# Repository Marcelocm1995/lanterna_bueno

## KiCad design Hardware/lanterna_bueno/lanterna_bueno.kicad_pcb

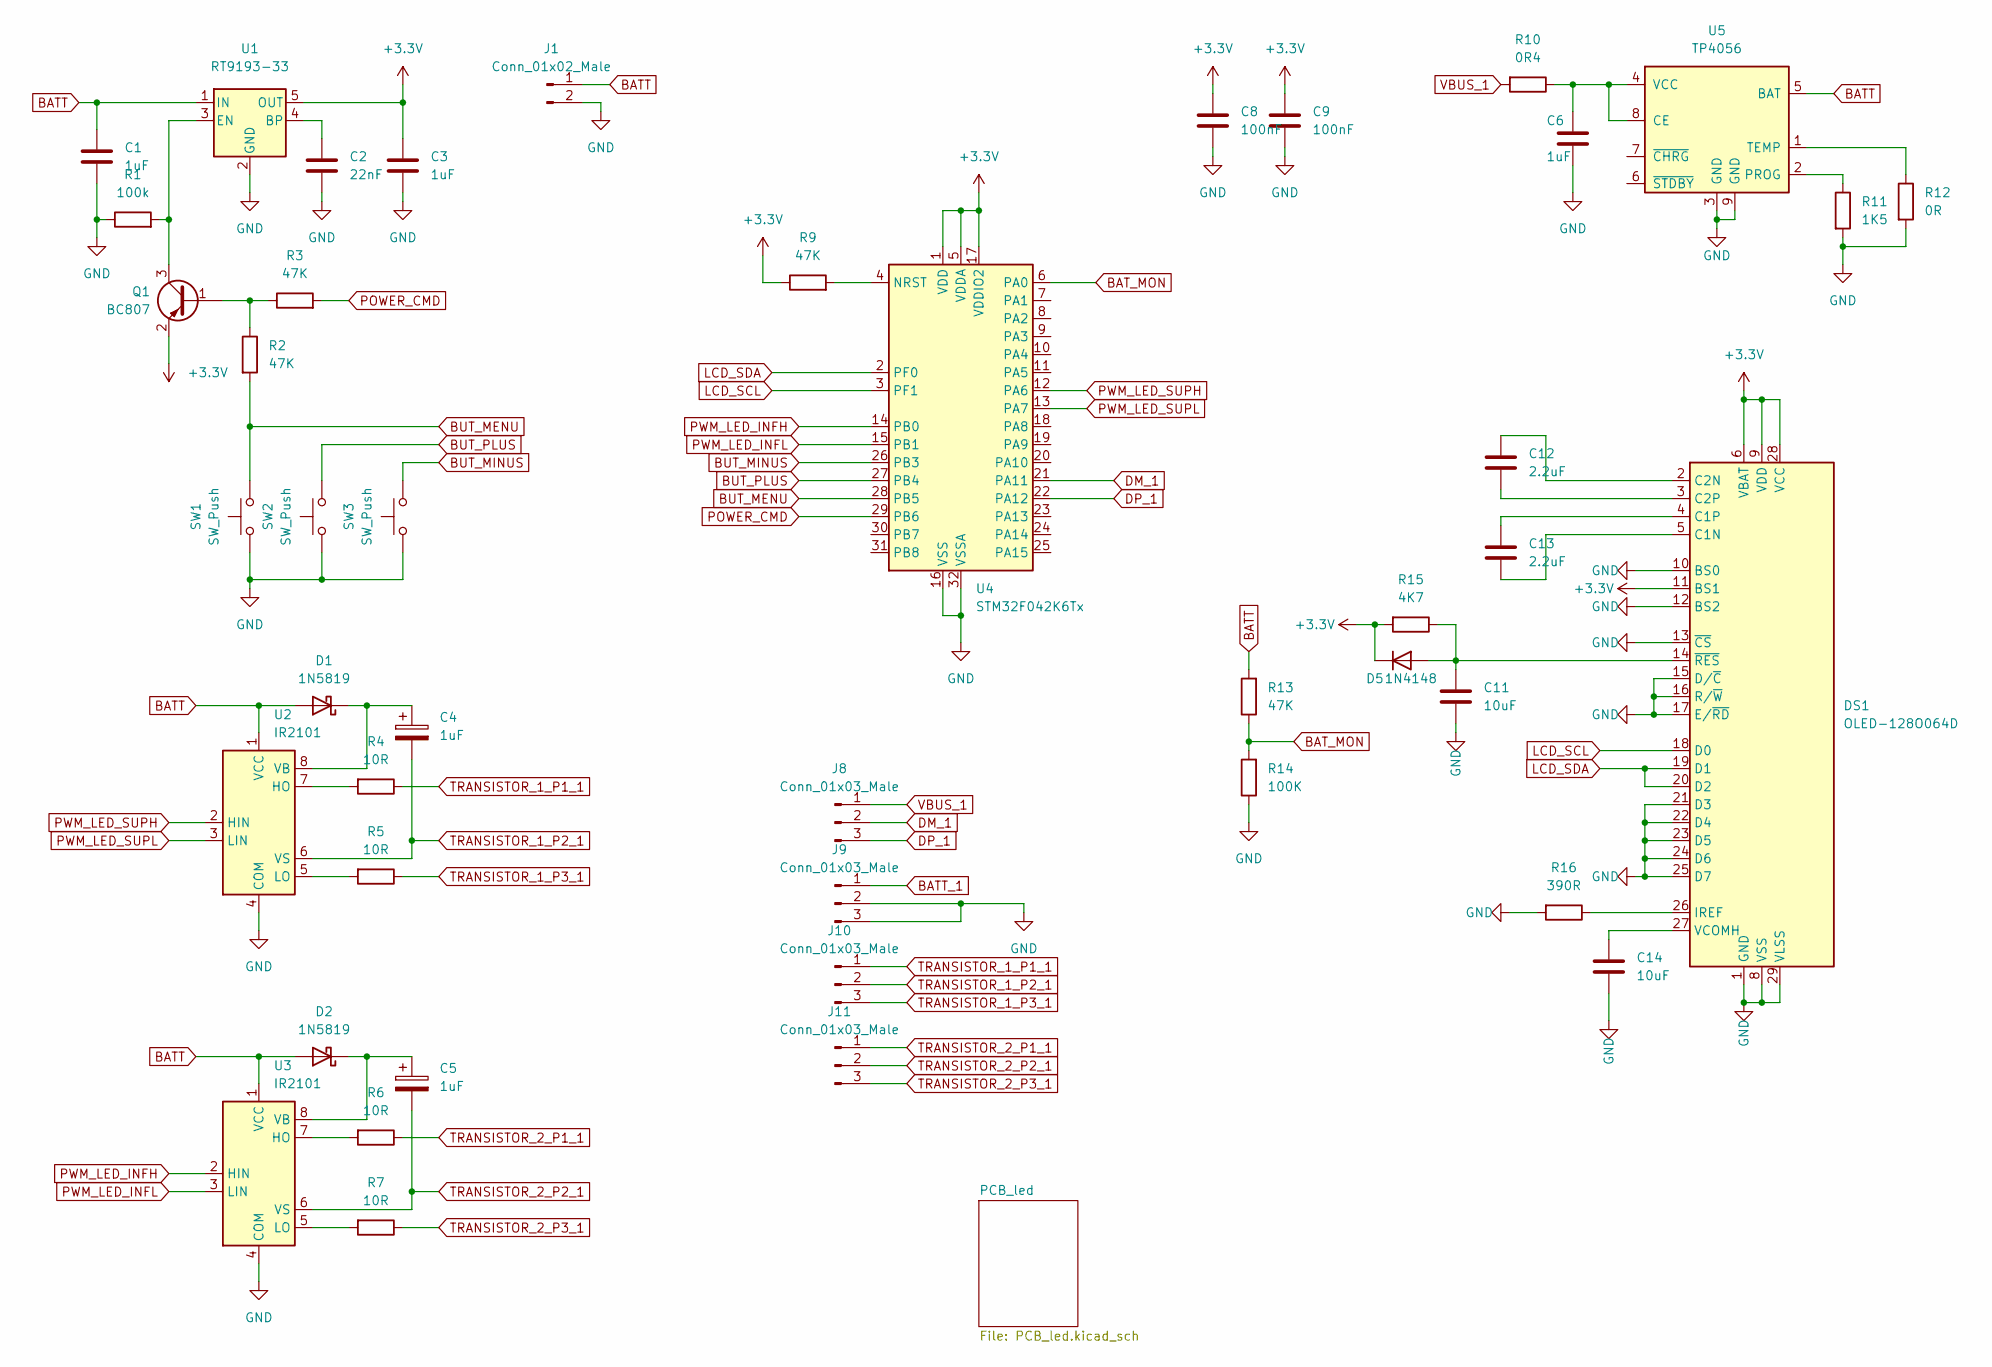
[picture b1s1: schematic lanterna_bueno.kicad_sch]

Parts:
C1, C3, C6: 1uF; C_1206_3216Metric
C2: 22nF; C_0603_1608Metric
C4, C5: 1uF; CP_Elec_4x3
C8, C9: 100nF; C_0603_1608Metric
C11, C14: 10uF; C_1206_3216Metric
C12, C13: 2.2uF; C_0603_1608Metric
D1, D2: 1N5819; D_SMA
D5: 1N4148; D_SOD-123
DS1: OLED-128O064D
J1: Conn_01x02_Male; SMD_BAT
J8, J9, J10, J11: Conn_01x03_Male; 3pin 90 pcb solder
Q1: BC807; SOT-23
R1: 100k; R_0603_1608Metric
R2, R3, R9, R13: 47K; R_0603_1608Metric
R4, R5, R6, R7: 10R; R_0603_1608Metric
R10: 0R4; R_0603_1608Metric
R11: 1K5; R_0603_1608Metric
R12: 0R; R_0603_1608Metric
R14: 100K; R_0603_1608Metric
R15: 4K7; R_0603_1608Metric
R16: 390R; R_0603_1608Metric
SW1, SW2, SW3: SW_Push; SW_Push_1P1T_NO_6x6mm_H9.5mm
U1: RT9193-33; SOT-23-5
U2, U3: IR2101; SOIC-8_3.9x4.9mm_P1.27mm
U4: STM32F042K6Tx; LQFP-32_7x7mm_P0.8mm
U5: TP4056; Infineon_PG-DSO-8-43

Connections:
+3V3: C3.1, C8.1, C9.1, D5.1 (K), DS1.6 (VBAT), DS1.9 (VDD), DS1.11 (BS1), DS1.28 (VCC), Q1.2 (E), R9.1, R15.2, U1.5 (OUT), U4.1 (VDD), U4.5 (VDDA), U4.17 (VDDIO2)
BATT: C1.1, D1.2 (A), D2.2 (A), J1.1, R13.2, U1.1 (IN), U2.1 (VCC), U3.1 (VCC), U5.5 (BAT)
BATT_1: J9.1
BAT_MON: R13.1, R14.2, U4.6 (PA0)
BUT_MENU: R2.2, SW1.2, U4.28 (PB5)
BUT_MINUS: SW3.2, U4.26 (PB3)
BUT_PLUS: SW2.2, U4.27 (PB4)
DM_1: J8.2, U4.21 (PA11)
DP_1: J8.3, U4.22 (PA12)
GND: C1.2, C2.2, C3.2, C6.2, C8.2, C9.2, C11.2, C14.2, DS1.1 (GND), DS1.8 (VSS), DS1.10 (BS0), DS1.12 (BS2), DS1.13 (~CS), DS1.15 (D/~C), DS1.16 (R/~W), DS1.17 (E/~RD), DS1.21 (D3), DS1.22 (D4), DS1.23 (D5), DS1.24 (D6), DS1.25 (D7), DS1.29 (VLSS), DS1.30 (GND), J1.2, J9.2, J9.3, R1.1, R11.2, R12.2, R14.1, R16.2, SW1.1, SW2.1, SW3.1, U1.2 (GND), U2.4 (COM), U3.4 (COM), U4.16 (VSS), U4.32 (VSSA), U5.3 (GND), U5.9 (GND)
LCD_SCL: DS1.18 (D0), U4.3 (PF1)
LCD_SDA: DS1.19 (D1), DS1.20 (D2), U4.2 (PF0)
unnamed: C2.1, U1.4 (BP)
unnamed: C4.1, D1.1 (K), U2.8 (VB)
unnamed: C5.1, D2.1 (K), U3.8 (VB)
unnamed: C6.1, R10.1, U5.4 (VCC), U5.8 (CE)
unnamed: C11.1, D5.2 (A), DS1.14 (~RES), R15.1
unnamed: C12.1, DS1.2 (C2N)
unnamed: C12.2, DS1.3 (C2P)
unnamed: C13.1, DS1.4 (C1P)
unnamed: C13.2, DS1.5 (C1N)
unnamed: C14.1, DS1.27 (VCOMH)
unnamed: DS1.26 (IREF), R16.1
unnamed: Q1.1 (B), R2.1, R3.1
unnamed: Q1.3 (C), R1.2, U1.3 (EN)
unnamed: R4.2, U2.7 (HO)
unnamed: R5.2, U2.5 (LO)
unnamed: R6.2, U3.7 (HO)
unnamed: R7.2, U3.5 (LO)
unnamed: R9.2, U4.4 (NRST)
unnamed: R11.1, U5.2 (PROG)
unnamed: R12.1, U5.1 (TEMP)
POWER_CMD: R3.2, U4.29 (PB6)
PWM_LED_INFH: U3.2 (HIN), U4.14 (PB0)
PWM_LED_INFL: U3.3 (LIN), U4.15 (PB1)
PWM_LED_SUPH: U2.2 (HIN), U4.12 (PA6)
PWM_LED_SUPL: U2.3 (LIN), U4.13 (PA7)
TRANSISTOR_1_P1_1: J10.1, R4.1
TRANSISTOR_1_P2_1: C4.2, J10.2, U2.6 (VS)
TRANSISTOR_1_P3_1: J10.3, R5.1
TRANSISTOR_2_P1_1: J11.1, R6.1
TRANSISTOR_2_P2_1: C5.2, J11.2, U3.6 (VS)
TRANSISTOR_2_P3_1: J11.3, R7.1
VBUS_1: J8.1, R10.2

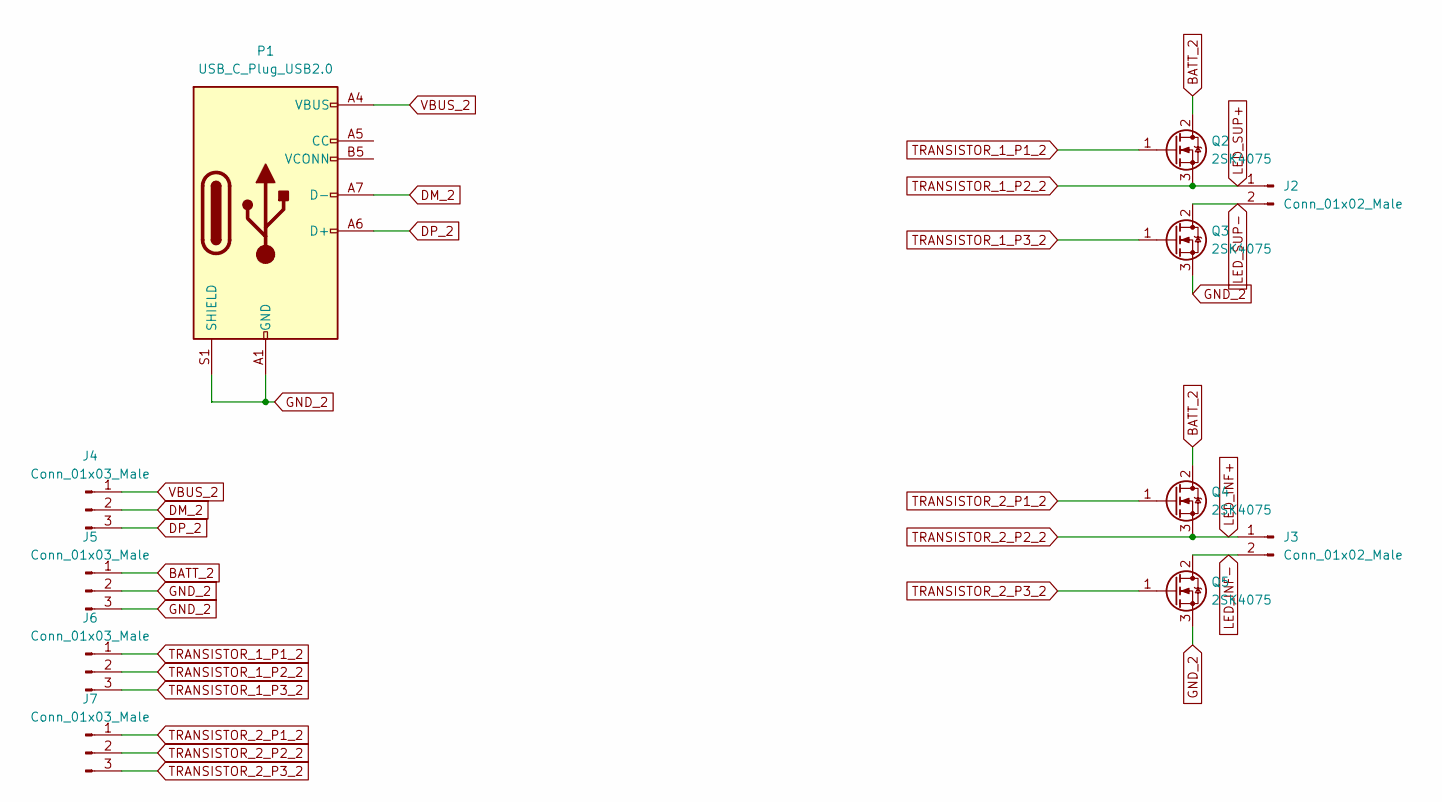
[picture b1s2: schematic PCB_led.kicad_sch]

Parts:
J2, J3: Conn_01x02_Male; SMD_BAT
J4, J5, J6, J7: Conn_01x03_Male; 3pin 90 pcb solder
P1: USB_C_Plug_USB2.0; USB_C_Receptacle_HRO_TYPE-C-31-M-12
Q2, Q3, Q4, Q5: 2SK4075; TO-252-2

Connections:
BATT_2: J5.1, Q2.2 (D), Q4.2 (D)
DM_2: J4.2, P1.A7 (D-)
DP_2: J4.3, P1.A6 (D+)
GND_2: J5.2, J5.3, P1.A1 (GND), P1.A12 (GND), P1.B1 (GND), P1.B12 (GND), P1.S1 (SHIELD), Q3.3 (S), Q5.3 (S)
LED_INF+: J3.1, J7.2, Q4.3 (S)
LED_INF-: J3.2, Q5.2 (D)
LED_SUP+: J2.1, J6.2, Q2.3 (S)
LED_SUP-: J2.2, Q3.2 (D)
TRANSISTOR_1_P1_2: J6.1, Q2.1 (G)
TRANSISTOR_1_P3_2: J6.3, Q3.1 (G)
TRANSISTOR_2_P1_2: J7.1, Q4.1 (G)
TRANSISTOR_2_P3_2: J7.3, Q5.1 (G)
VBUS_2: J4.1, P1.A4 (VBUS), P1.A9 (VBUS), P1.B4 (VBUS), P1.B9 (VBUS)

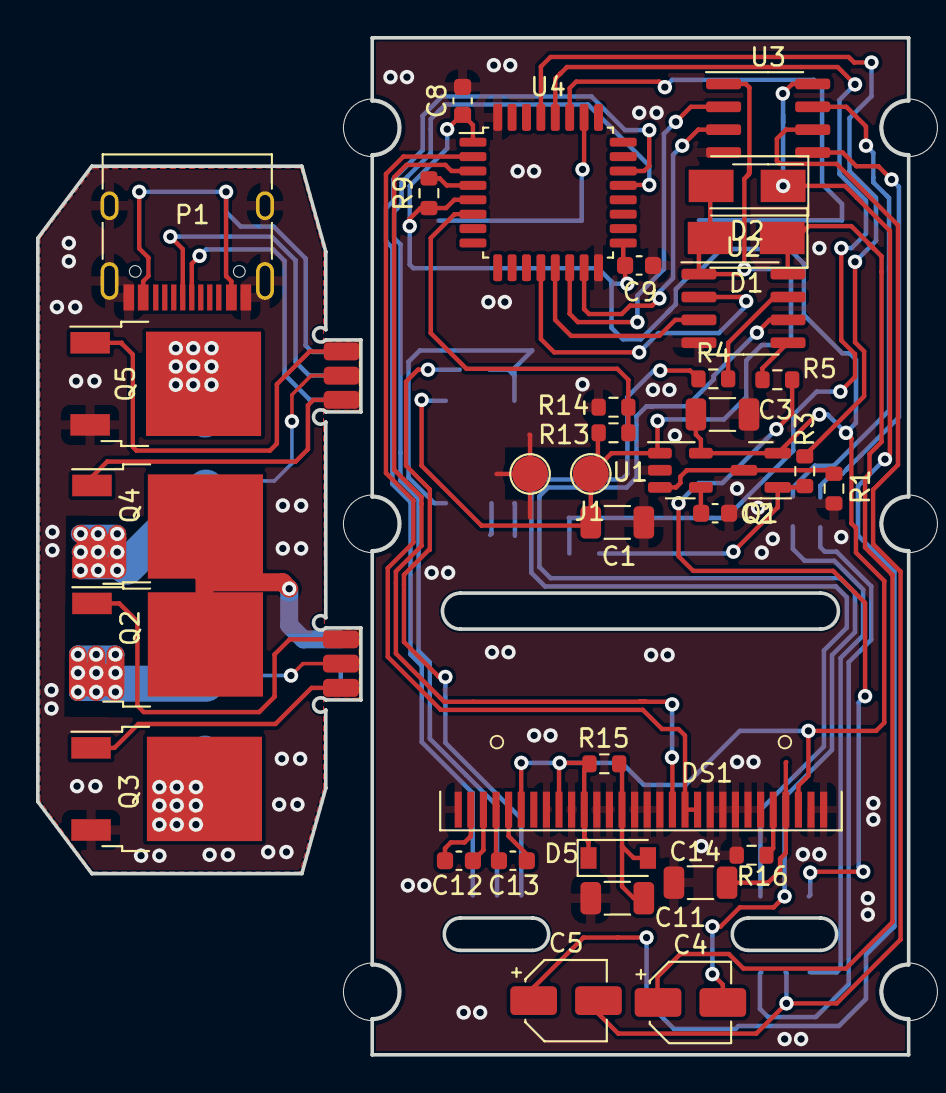
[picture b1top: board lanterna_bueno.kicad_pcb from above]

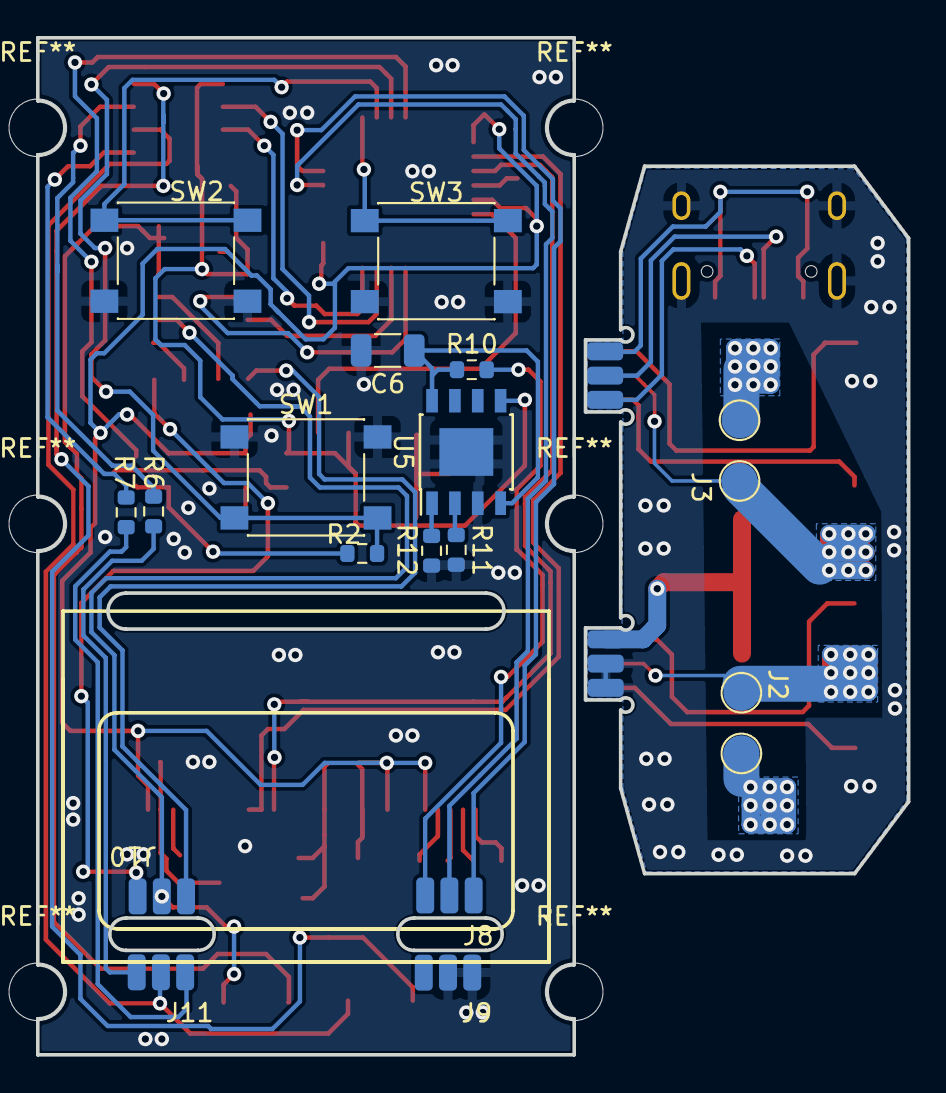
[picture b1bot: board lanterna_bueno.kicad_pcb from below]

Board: 2 copper layers, 48.4 x 56.5 mm, 56 parts (19 on the bottom side), 56 nets.

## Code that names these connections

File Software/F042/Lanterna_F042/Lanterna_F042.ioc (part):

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Mcu.Name=STM32F042K(4-6)Tx
Mcu.Package=LQFP32
Mcu.UserName=STM32F042K6Tx
PA0.GPIOParameters=GPIO_Label
PA0.GPIO_Label=BAT_MON
PA0.Mode=IN0
PA0.Signal=ADC_IN0
PA11.Mode=Device
PA11.Signal=USB_DM
PA12.Mode=Device
PA12.Signal=USB_DP
PA6.GPIOParameters=GPIO_Label
PA6.GPIO_Label=PWM_LED_SUPH
PA6.Signal=S_TIM3_CH1
PA7.GPIOParameters=GPIO_Label
PA7.GPIO_Label=PWM_LED_SUPL
PA7.Signal=S_TIM3_CH2
PB0.GPIOParameters=GPIO_Label
PB0.GPIO_Label=PWM_LED_INFH
PB0.Mode=PWM Generation2 CH2N
PB0.Signal=TIM1_CH2N
PB1.GPIOParameters=GPIO_Label
PB1.GPIO_Label=PWM_LED_INFL
PB1.Mode=PWM Generation3 CH3N
PB1.Signal=TIM1_CH3N
PB3.GPIOParameters=GPIO_Label
PB3.GPIO_Label=BUT_MINUS
PB3.Signal=GPIO_Input
PB4.GPIOParameters=GPIO_Label
PB4.GPIO_Label=BUT_PLUS
PB4.Signal=GPIO_Input
PB5.GPIOParameters=GPIO_Label
PB5.GPIO_Label=BUT_MENU
PB5.Signal=GPIO_Input
PB6.GPIOParameters=GPIO_Label
PB6.GPIO_Label=POWER_CMD
PB6.Signal=GPIO_Output
PF0-OSC_IN.Mode=I2C
PF0-OSC_IN.Signal=I2C1_SDA
PF1-OSC_OUT.Mode=I2C
PF1-OSC_OUT.Signal=I2C1_SCL
RCC.SYSCLKFreq_VALUE=48000000
RCC.SYSCLKSource=RCC_SYSCLKSOURCE_HSI48
board=custom

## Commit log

2022-05-09 building
2022-07-04 add Mechanical DXF
2022-07-05 Starting board, mounting holes OK
2022-07-06 Flat do Oled posicionado
2022-07-08 Adicionado PCB Carga e Board Profile corrigido
2022-07-13 Usb PCB Chamfer
2022-07-13 usb c
    falta posicionar
2022-07-13 USB-B to USB-C
2022-07-13 building pcb
2022-07-26 buidlging
